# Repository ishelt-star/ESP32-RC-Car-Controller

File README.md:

# ESP32 RC Car Control System

## Project Overview

Designed a custom electronic control system for a remote-controlled car, consisting of an ESP32-based transmitter and a receiver/motor controller. The project focuses on PCB design, power regulation, microcontroller integration, and brushed DC motor control.

Both circuits were developed using KiCad, with custom schematics and PCB layouts.

## Receiver and Motor Controller

The receiver board integrates several electrical subsystems:

- **ESP32 DevKitC:** Microcontroller interface for motor speed, direction, and steering control.
- **MOSFET H-Bridge:** Discrete switching circuit designed for bidirectional control of a brushed DC motor.
- **Power Regulation:** 7.4V nominal (2S) LiPo battery input with 5V linear voltage regulation.
- **Servo Interface:** Three-pin connector for steering servo control.
- **Circuit Protection and Filtering:** Bulk and decoupling capacitors incorporated into the power distribution design.

## Transmitter

Designed a separate ESP32-based transmitter circuit featuring:

- Joystick inputs for throttle and steering commands.
- ESP32 microcontroller for reading user inputs.
- Power regulation and supporting circuitry.
- Custom PCB schematic and layout.

## Engineering Tools and Skills

- KiCad schematic capture and PCB layout
- Circuit analysis and component selection
- MOSFET switching circuit design
- Microcontroller interfacing
- Power distribution and voltage regulation
- Hardware documentation

## Project Status

PCB design and documentation stage. Physical assembly, firmware validation, and hardware testing are not yet documented.

## Future Development

- Assemble and test the transmitter and receiver boards.
- Develop and validate wireless communication and control firmware.
- Test motor switching, steering response, and power regulation.
- Evaluate circuit performance and refine the hardware design.

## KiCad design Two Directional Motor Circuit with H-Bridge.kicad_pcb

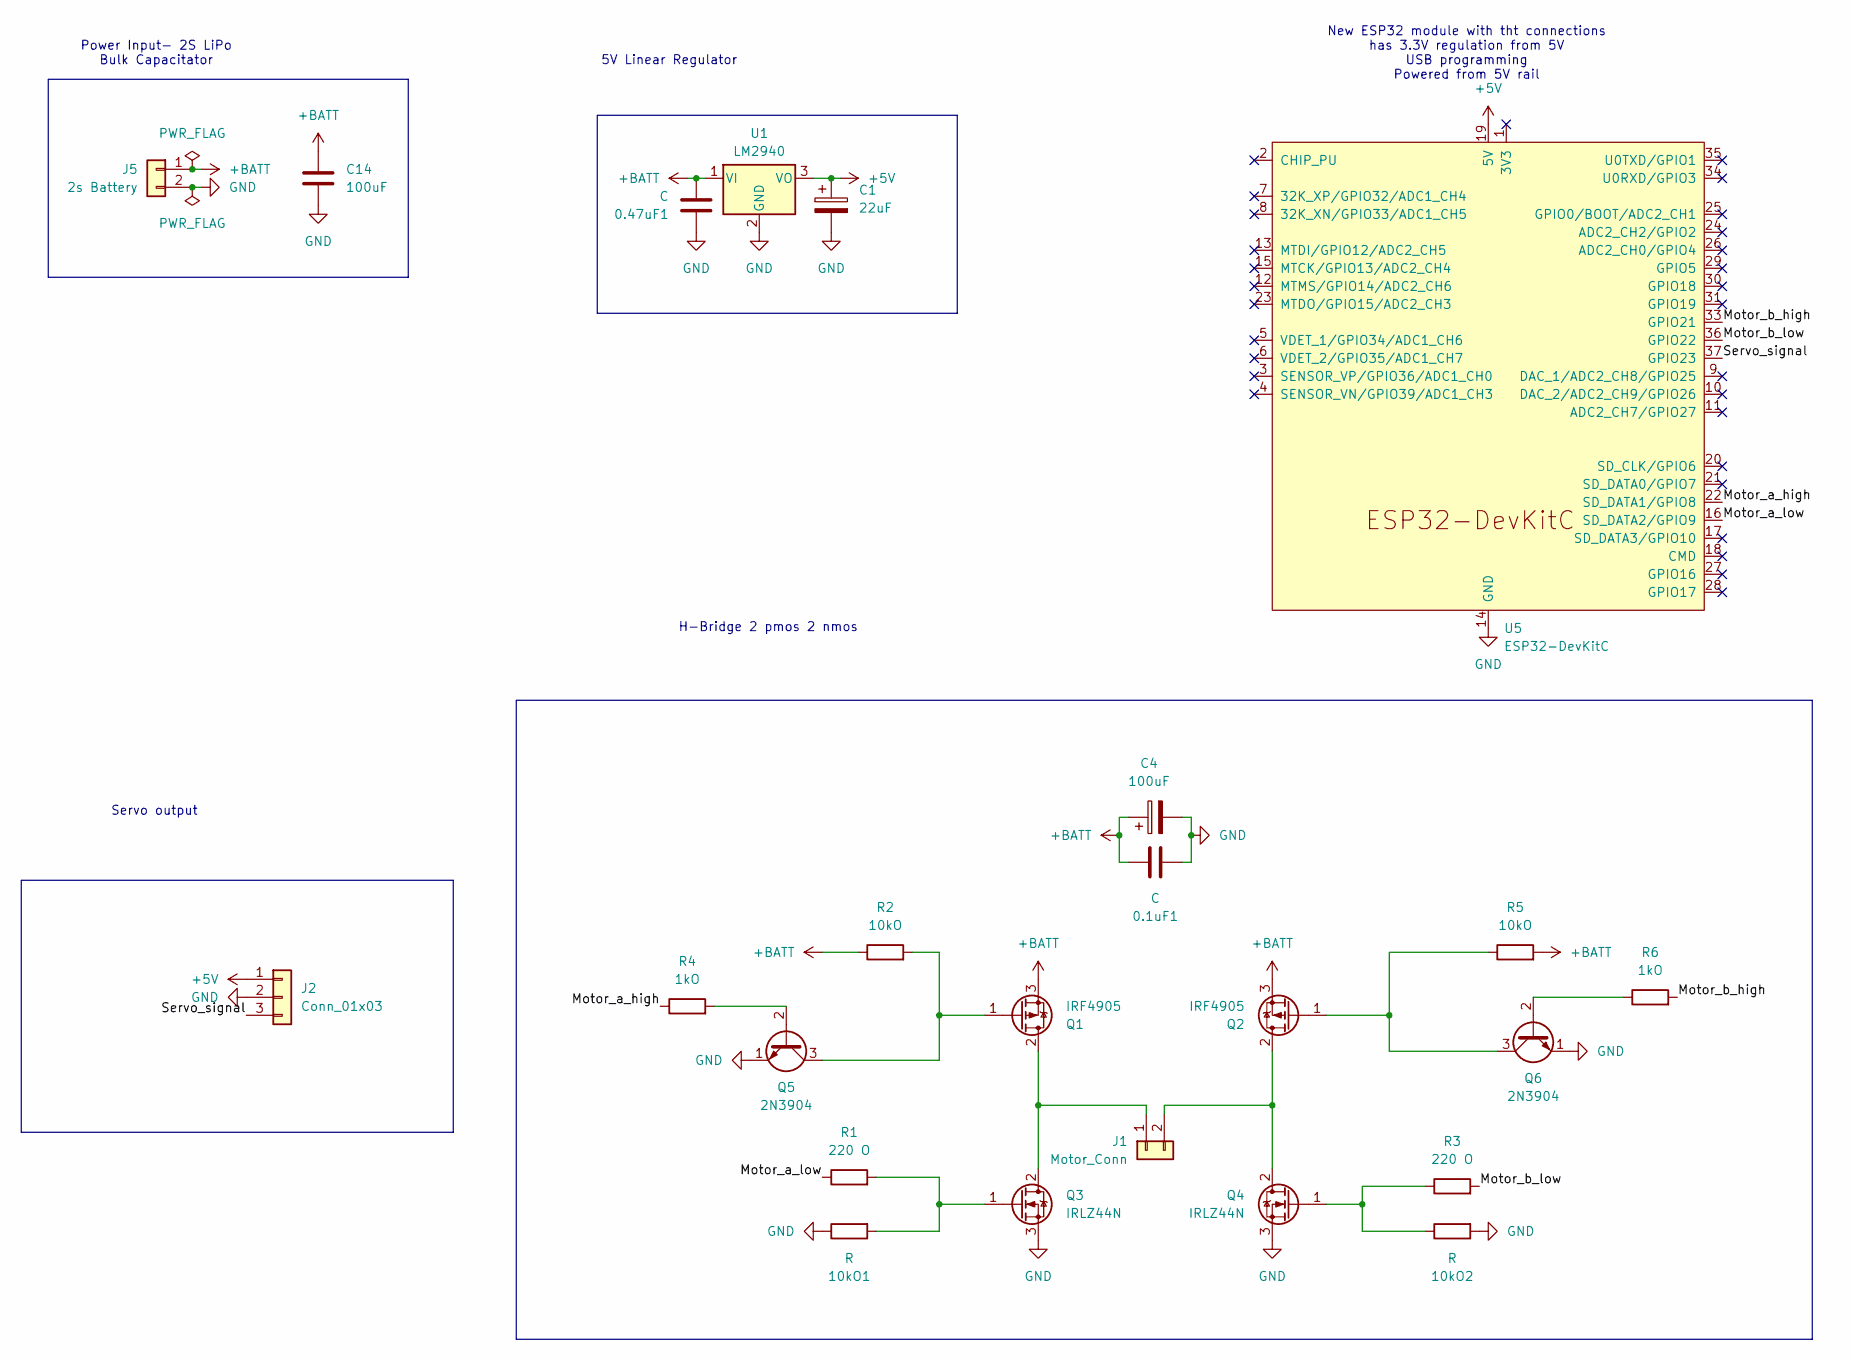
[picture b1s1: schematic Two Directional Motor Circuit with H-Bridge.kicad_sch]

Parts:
0.1uF1, 0.47uF1: C; C_Disc_D5.0mm_W2.5mm_P5.00mm
10kO1, 10kO2: R; R_Axial_DIN0207_L6.3mm_D2.5mm_P10.16mm_Horizontal
C1: 22uF; CP_Radial_D6.3mm_P2.50mm
C4, C14: 100uF; CP_Radial_D6.3mm_P2.50mm
J1: Motor_Conn; TerminalBlock_Phoenix_MKDS-1,5-2_1x02_P5.00mm_Horizontal
J2: Conn_01x03; PinHeader_1x03_P2.54mm_Vertical
J5: 2s Battery; TerminalBlock_Phoenix_MKDS-1,5-2_1x02_P5.00mm_Horizontal
Q1, Q2: IRF4905; TO-220-3_Vertical
Q3, Q4: IRLZ44N; TO-220-3_Vertical
Q5, Q6: 2N3904; TO-92_Inline
R1, R3: 220 O; R_Axial_DIN0207_L6.3mm_D2.5mm_P10.16mm_Horizontal
R2, R5: 10kO; R_Axial_DIN0207_L6.3mm_D2.5mm_P10.16mm_Horizontal
R4, R6: 1kO; R_Axial_DIN0207_L6.3mm_D2.5mm_P10.16mm_Horizontal
U1: LM2940; TO-220-3_Vertical
U5: ESP32-DevKitC

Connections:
+5V: C1.1, J2.1, U1.3 (VO), U5.19 (5V)
+BATT: 0.1uF1.1, 0.47uF1.2, C4.1, C14.1, J5.1, Q1.3 (S), Q2.3 (S), R2.1, R5.2, U1.1 (VI)
/Motor_a_high: R4.1, U5.22 (SD_DATA1/GPIO8)
/Motor_a_low: R1.1, U5.16 (SD_DATA2/GPIO9)
/Motor_b_high: R6.2, U5.33 (GPIO21)
/Motor_b_low: R3.2, U5.36 (GPIO22)
/Servo_signal: J2.3, U5.37 (GPIO23)
GND: 0.1uF1.2, 0.47uF1.1, 10kO1.1, 10kO2.2, C1.2, C4.2, C14.2, J2.2, J5.2, Q3.3 (S), Q4.3 (S), Q5.1 (E), Q6.1 (E), U1.2 (GND), U5.14 (GND), U5.32 (GND), U5.38 (GND)
unnamed: J1.1, Q1.2 (D), Q3.2 (D)
unnamed: J1.2, Q2.2 (D), Q4.2 (D)
unnamed: Q1.1 (G), Q5.3 (C), R2.2
unnamed: Q2.1 (G), Q6.3 (C), R5.1
unnamed: 10kO1.2, Q3.1 (G), R1.2
unnamed: 10kO2.1, Q4.1 (G), R3.1
unnamed: Q5.2 (B), R4.2
unnamed: Q6.2 (B), R6.1

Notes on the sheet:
New ESP32 module with tht connections has 3.3V regulation from 5V USB programming Powered from 5V rail
Servo output
5V Linear Regulator
H-Bridge 2 pmos 2 nmos
Power Input- 2S LiPo Bulk Capacitator

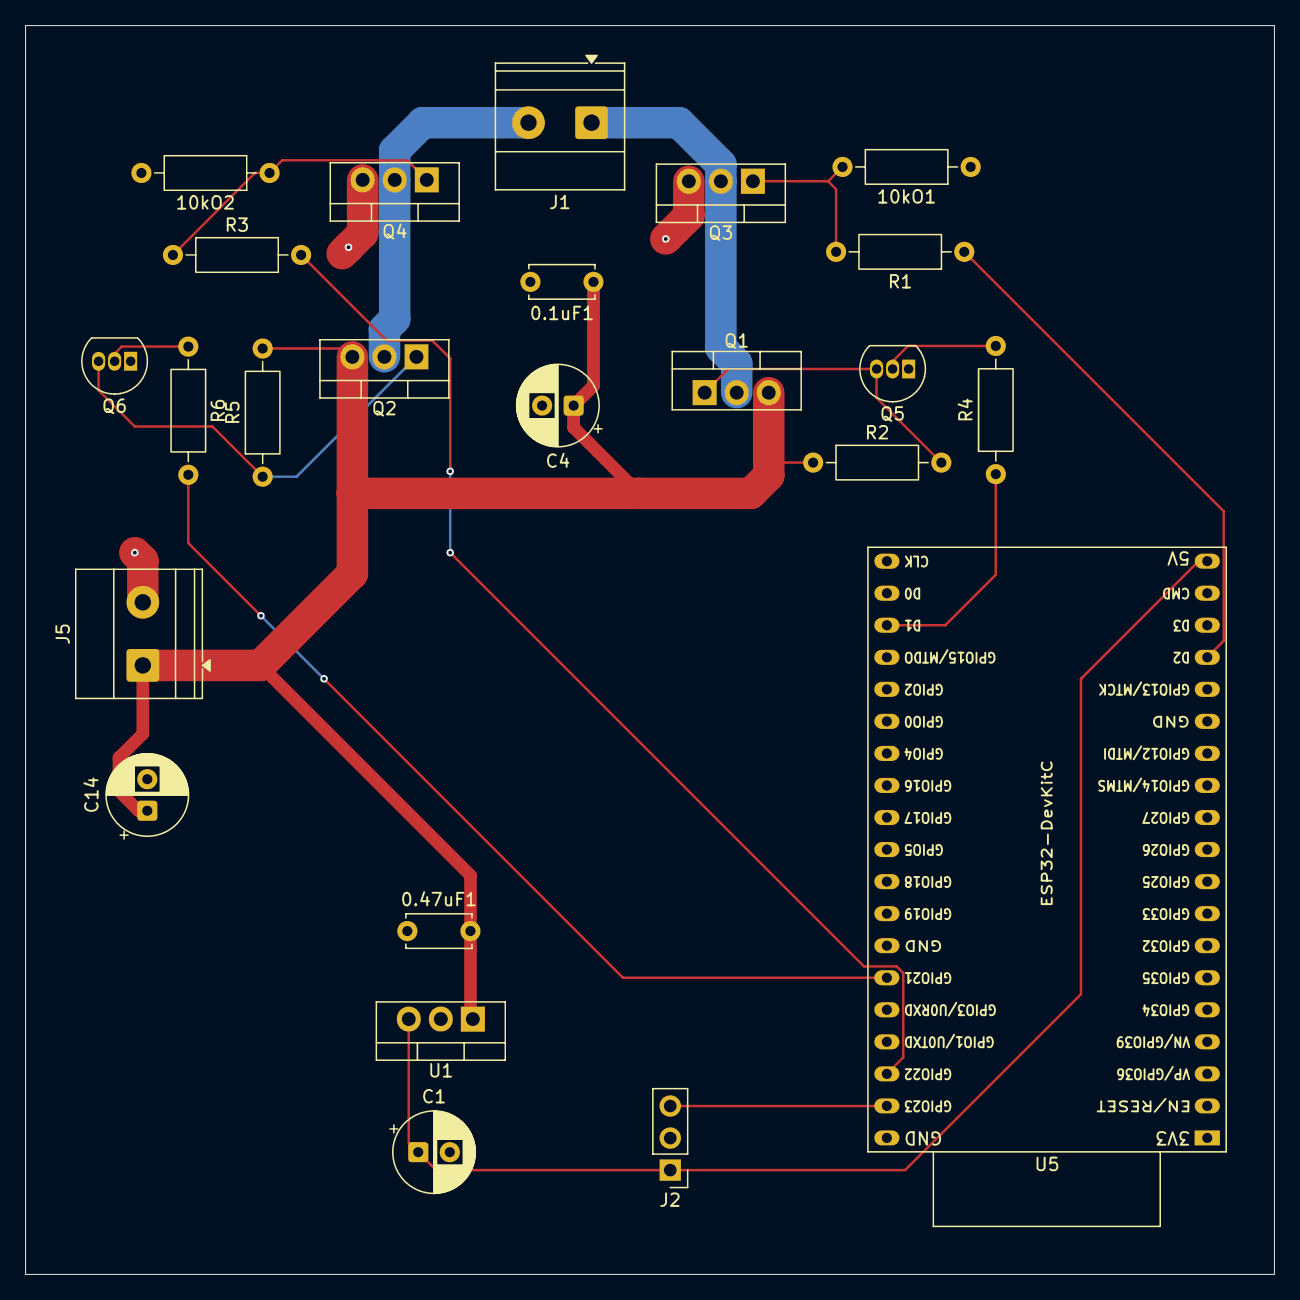
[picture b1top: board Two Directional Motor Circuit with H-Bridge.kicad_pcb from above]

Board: 2 copper layers, 99.0 x 99.0 mm, 24 parts (0 on the bottom side), 16 nets.

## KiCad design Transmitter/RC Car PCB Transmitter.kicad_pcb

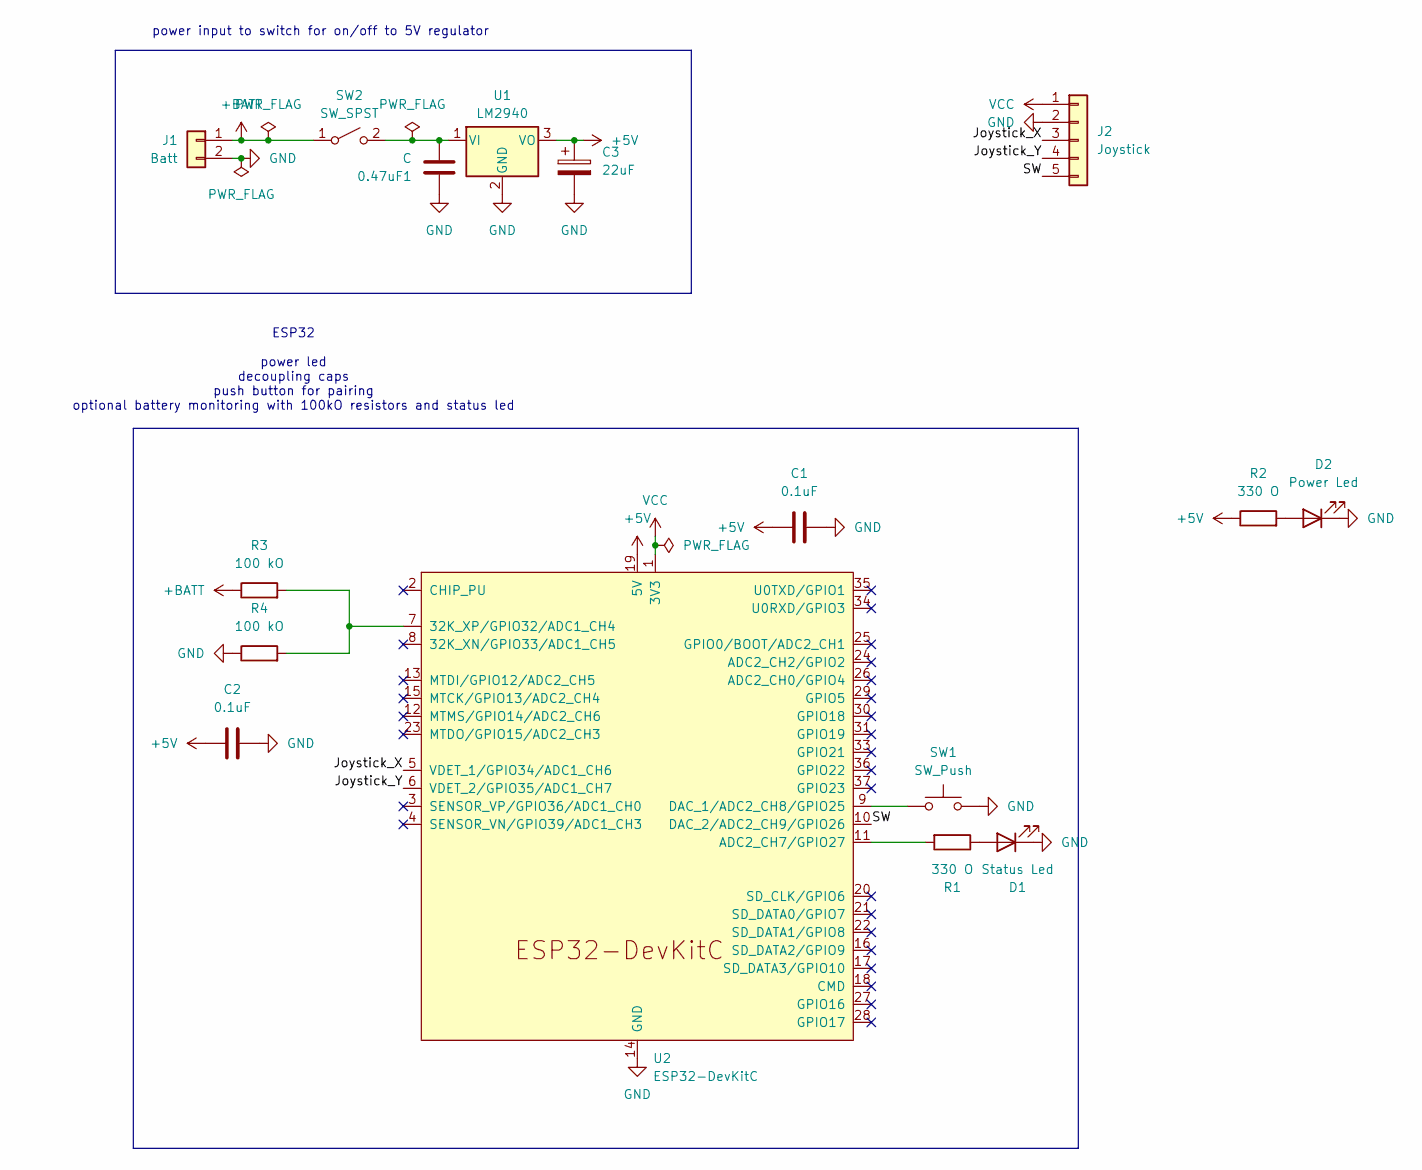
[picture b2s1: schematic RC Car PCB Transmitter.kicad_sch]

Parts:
0.47uF1: C; C_Disc_D5.0mm_W2.5mm_P5.00mm
C1, C2: 0.1uF; C_Disc_D5.0mm_W2.5mm_P5.00mm
C3: 22uF; CP_Radial_D6.3mm_P2.50mm
D1: Status Led; LED_D5.0mm
D2: Power Led; LED_D5.0mm
J1: Batt; TerminalBlock_Phoenix_MKDS-1,5-2-5.08_1x02_P5.08mm_Horizont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
J2: Joystick; PinHeader_1x05_P2.54mm_Vertical
R1, R2: 330 O; R_Axial_DIN0207_L6.3mm_D2.5mm_P10.16mm_Horizontal
R3, R4: 100 kO; R_Axial_DIN0207_L6.3mm_D2.5mm_P10.16mm_Horizontal
SW1: SW_Push; SW_CK_JS202011AQN_DPDT_Angled
SW2: SW_SPST; SW_CK_JS202011AQN_DPDT_Angled
U1: LM2940; TO-220-3_Vertical
U2: ESP32-DevKitC

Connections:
+5V: C1.1, C2.1, C3.1, R2.1, U1.3 (VO), U2.19 (5V)
+BATT: J1.1, R3.1, SW2.1 (A)
/Joystick_X: J2.3, U2.5 (VDET_1/GPIO34/ADC1_CH6)
/Joystick_Y: J2.4, U2.6 (VDET_2/GPIO35/ADC1_CH7)
/SW: J2.5, U2.10 (DAC_2/ADC2_CH9/GPIO26)
GND: 0.47uF1.1, C1.2, C2.2, C3.2, D1.1 (K), D2.1 (K), J1.2, J2.2, R4.1, SW1.2, U1.2 (GND), U2.14 (GND), U2.32 (GND), U2.38 (GND)
unnamed: D1.2 (A), R1.1
unnamed: D2.2 (A), R2.2
unnamed: 0.47uF1.2, SW2.2 (B), U1.1 (VI)
unnamed: R3.2, R4.2, U2.7 (32K_XP/GPIO32/ADC1_CH4)
unnamed: R1.2, U2.11 (ADC2_CH7/GPIO27)
unnamed: SW1.1, U2.9 (DAC_1/ADC2_CH8/GPIO25)
VCC: J2.1, U2.1 (3V3)

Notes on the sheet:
power input to switch for on/off to 5V regulator
ESP32 power led decoupling caps push button for pairing optional battery monitoring with 100kO resistors and status led

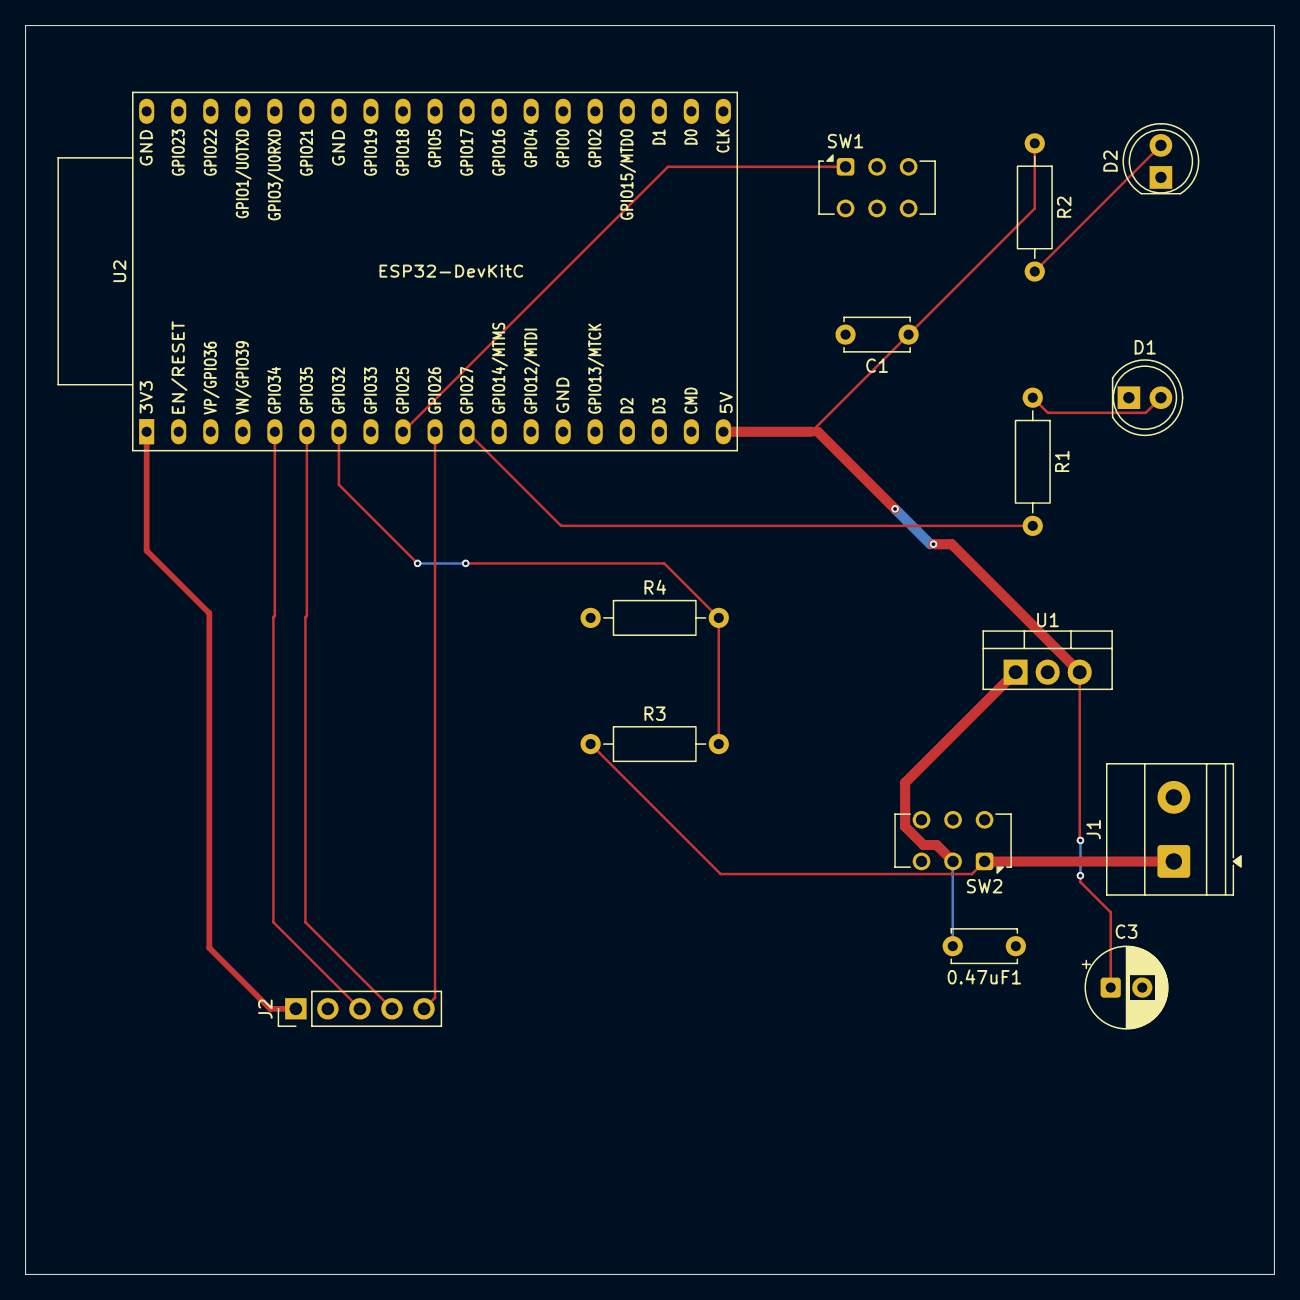
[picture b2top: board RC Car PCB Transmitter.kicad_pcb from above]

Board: 2 copper layers, 99.0 x 99.0 mm, 15 parts (0 on the bottom side), 13 nets.
